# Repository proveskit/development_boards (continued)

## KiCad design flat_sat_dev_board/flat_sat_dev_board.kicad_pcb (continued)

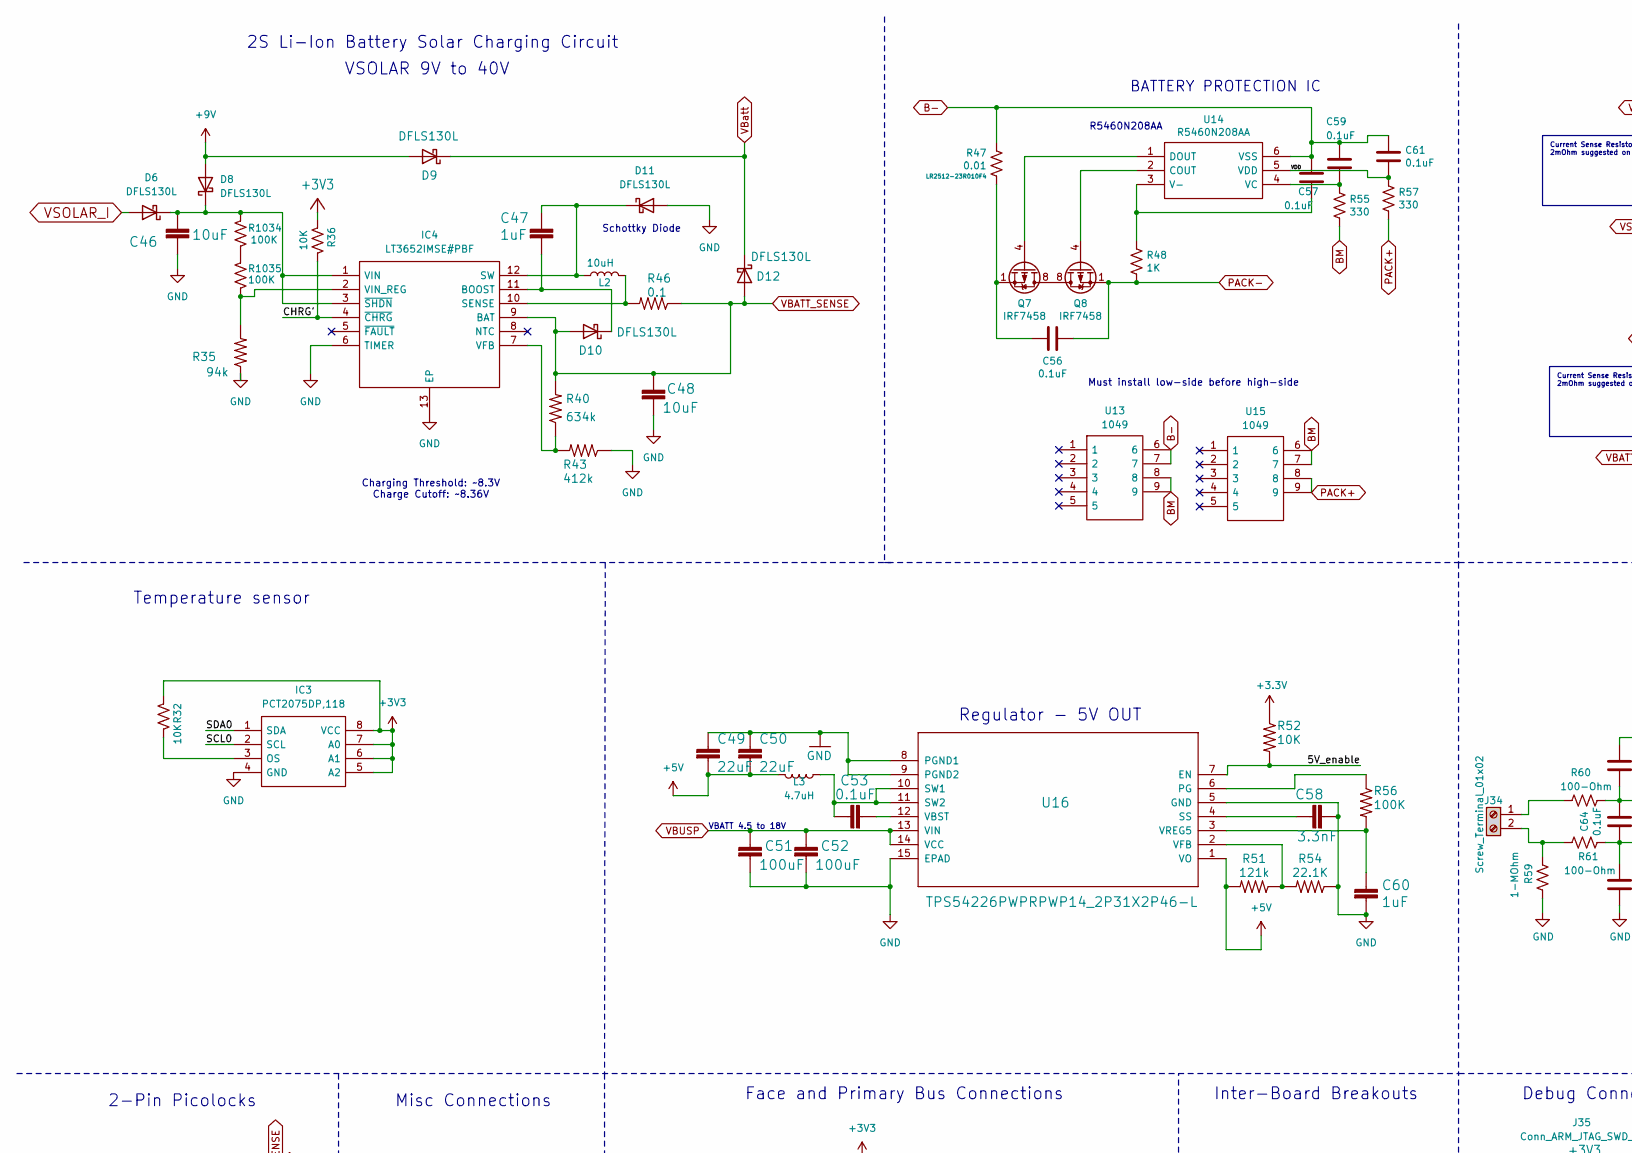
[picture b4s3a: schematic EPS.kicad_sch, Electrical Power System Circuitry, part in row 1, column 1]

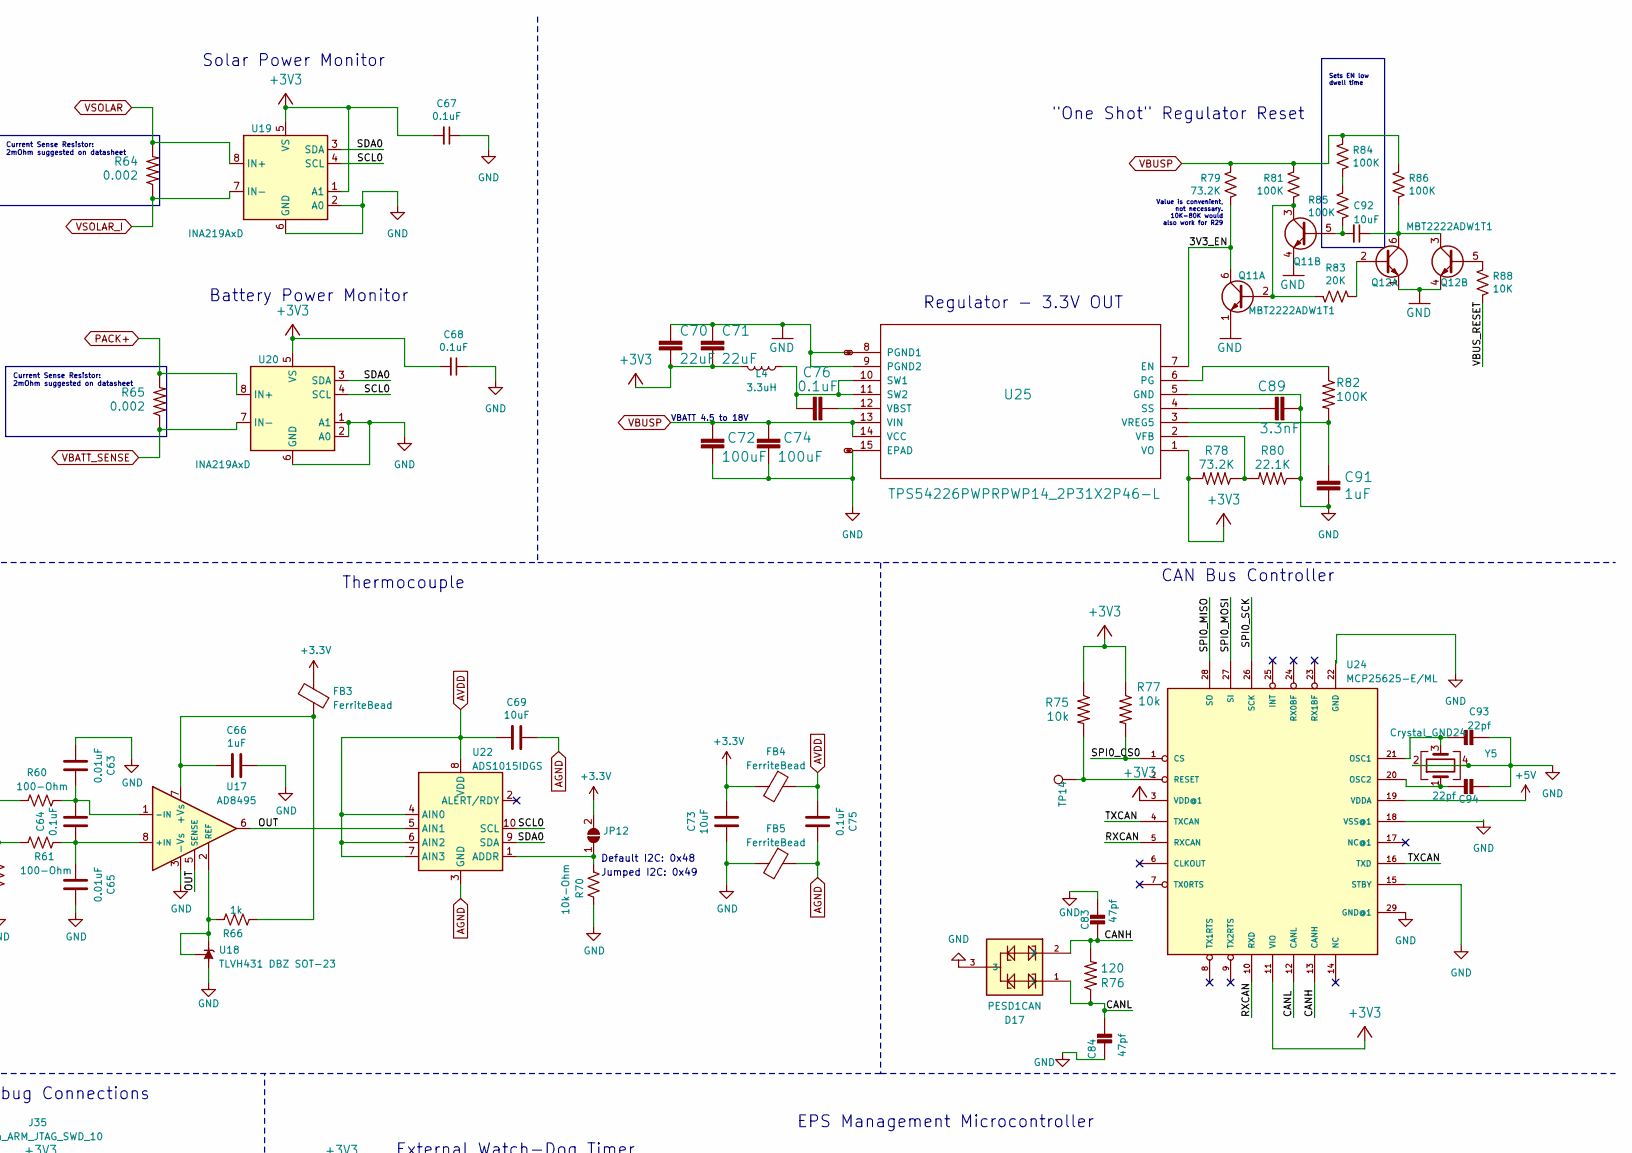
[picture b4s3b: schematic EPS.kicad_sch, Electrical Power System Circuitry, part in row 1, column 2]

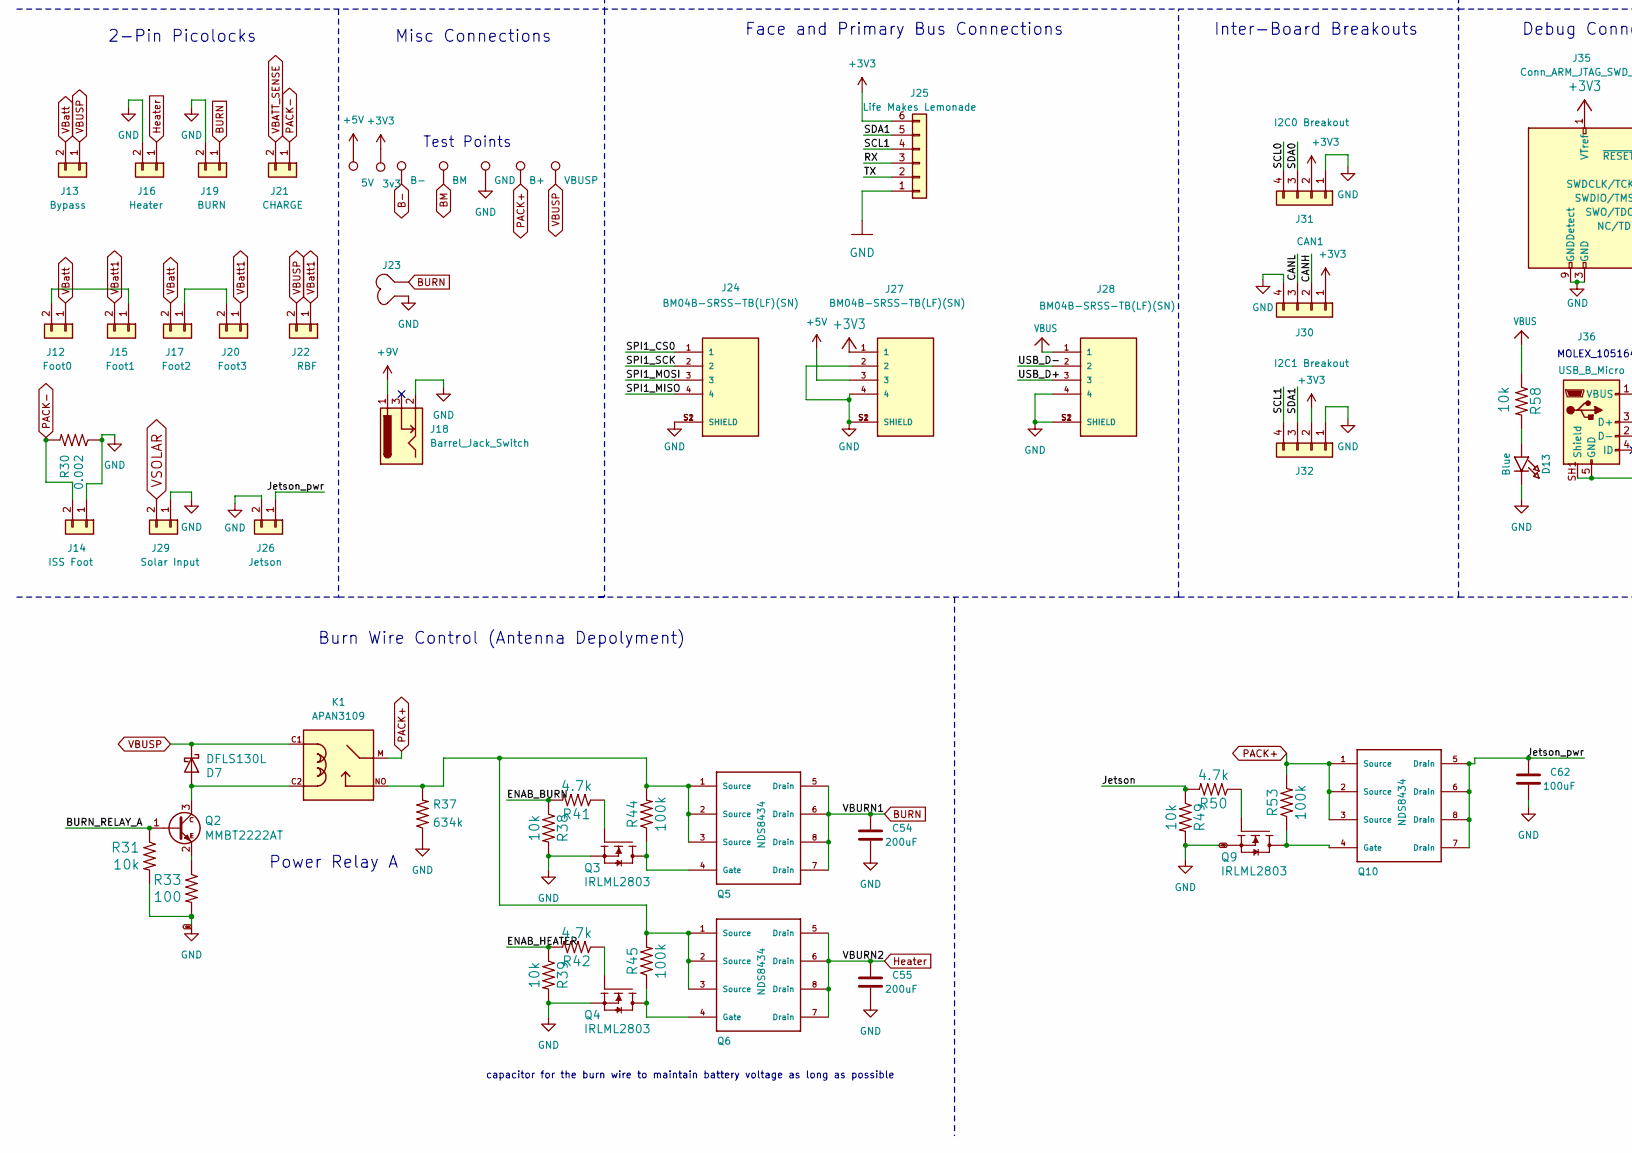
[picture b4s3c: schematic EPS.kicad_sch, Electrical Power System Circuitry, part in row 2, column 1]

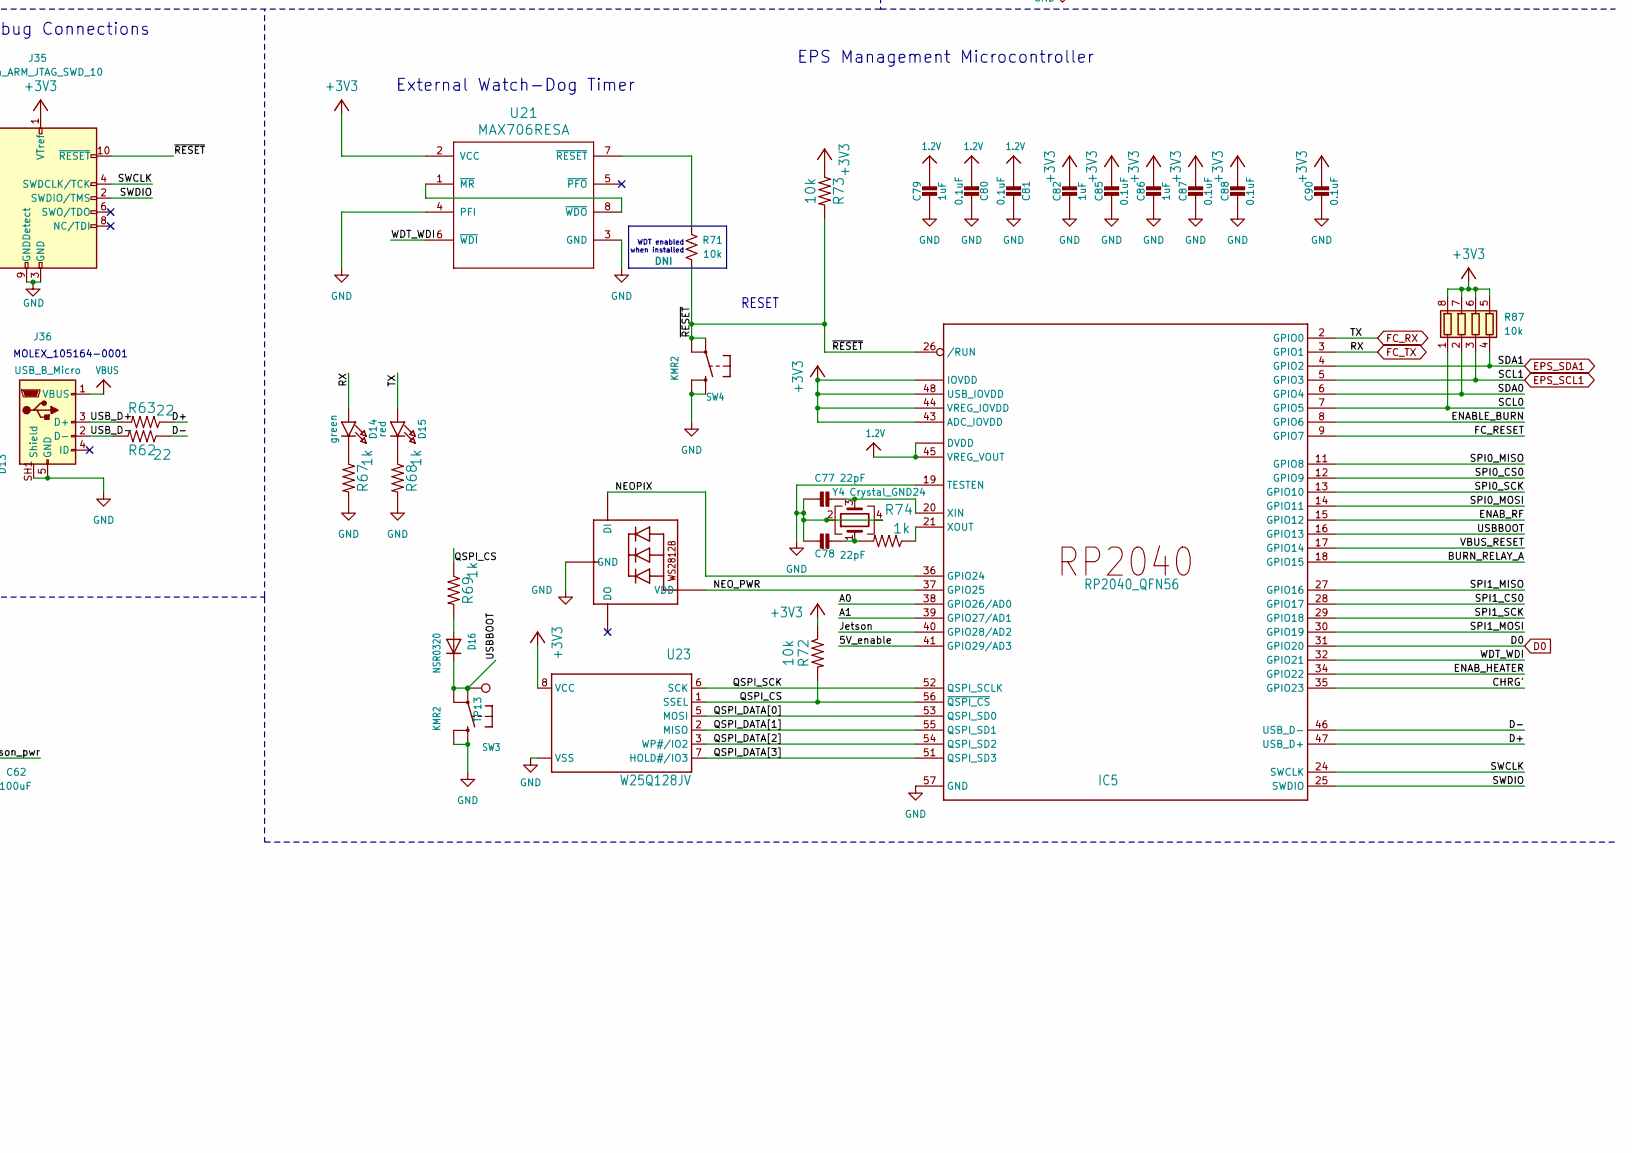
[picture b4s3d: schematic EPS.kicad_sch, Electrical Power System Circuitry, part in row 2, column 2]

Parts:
C46, C48, C92: 10uF; C_0603_1608Metric
C47, C60, C79, C82, C86, C91: 1uF; C_0603_1608Metric
C49, C50, C70, C71: 22uF; C_0603_1608Metric
C51, C52, C62, C72, C74: 100uF; C_1210_3225Metric
C53, C56, C57, C59, C61, C67, C68, C76: 0.1uF; C_0603_1608Metric
C54, C55: 200uF; C_1210_3225Metric
C58, C89: 3.3nF; C_0603_1608Metric
C63, C65: 0.01uF; C_0805_2012Metric
C64, C75: 0.1uF; C_0805_2012Metric
C66: 1uF; C_0805_2012Metric
C69, C73: 10uF; C_0805_2012Metric
C77, C78: 22pF; C_0402_1005Metric
C80, C81, C85, C87, C88, C90: 0.1uF; C_0402_1005Metric
C83, C84: 47pf; C_0402_1005Metric
C93, C94: 22pf; C_0402_1005Metric
D6, D8, D11: DFLS130L; D_PowerDI-123
D7, D9, D10, D12: DFLS130L; D_PowerDI-123; Manufacturer_Part_Number DFLS130L-7
D13: Blue; D_0603_1608Metric_Pad1.05x0.95mm_HandSolder
D14: green; D_0603_1608Metric_Pad1.05x0.95mm_HandSolder
D15: red; D_0603_1608Metric_Pad1.05x0.95mm_HandSolder
D16: NSR0320; D_SOD-323F
D17: PESD1CAN; SOT-23-3
FB3, FB4, FB5: FerriteBead; R_0603_1608Metric
IC3: PCT2075DP,118; TSSOP-8_3x3mm_P0.65mm; Mouser Part Number 771-PCT2075DP118
IC4: LT3652IMSE#PBF; MSOP-12-1EP_3x4mm_P0.65mm_EP1.65x2.85mm; Mouser Part Number 584-LT3652IMSE#PBF
IC5: RP2040_QFN56; QFN-56-1EP_7x7mm_P0.4mm_EP3.2x3.2mm
J12: Foot0; MOLEX_504050-0291
J13: Bypass; PinSocket_1x02_P2.54mm_Vertical
J14: ISS Foot; MOLEX_504050-0291
J15: Foot1; MOLEX_504050-0291
J16: Heater; MOLEX_504050-0291
J17: Foot2; MOLEX_504050-0291
J18: Barrel_Jack_Switch; BarrelJack_GCT_DCJ200-10-A_Horizontal
J19: BURN; MOLEX_504050-0291
J20: Foot3; MOLEX_504050-0291
J21: CHARGE; MOLEX_504050-0291
J22: RBF; MOLEX_504050-0291
J23: Burn_Wire
J24, J27, J28: BM04B-SRSS-TB(LF)(SN); JST_BM04B-SRSS-TB(LF)(SN); PARTREV N/A
J25: Life Makes Lemonade; PinHeader_1x06_P2.54mm_Vertical
J26: Jetson; MOLEX_504050-0291
J29: Solar Input; MOLEX_504050-0291
J30: CAN1; JST_SH_BM04B-SRSS-TB_1x04-1MP_P1.00mm_Vertical
J31: I2C0 Breakout; JST_SH_SM04B-SRSS-TB_1x04-1MP_P1.00mm_Horizontal
J32: I2C1 Breakout; JST_SH_BM04B-SRSS-TB_1x04-1MP_P1.00mm_Vertical
J34: Screw_Terminal_01x02; ScrewTerminal
J35: Conn_ARM_JTAG_SWD_10; JTAG_2X05_1.27MM_BOX_NOCREAM
J36: USB_B_Micro; MOLEX_105164-0001
JP12: SolderJumper_2_Open; SolderJumper-2_P1.3mm_Open_RoundedPad1.0x1.5mm
K1: APAN3109; RELAY_APAN3105
L2: 10uH; L_1812_4532Metric; Manufacturer_Part_Number SNR5040K-330M
L3: 4.7uH; L_1812_4532Metric; Manufacturer_Part_Number HPC5040NF-3R3MTH
L4: 3.3uH; L_1812_4532Metric; Manufacturer_Part_Number HPC5040NF-3R3MTH
LED2: WS2812B_SK6812_1515; LED_WS2812B_PLCC4_5.0x5.0mm_P3.2mm
Q2: MMBT2222AT; SOT-523; Manufacturer_Part_Number MMBT2222ALT1G
Q3, Q4, Q9: IRLML2803; SOT-23; Manufacturer_Part_Number MMBT2222AT
Q5, Q6, Q10: NDS8434; SOIC-8-1EP_3.9x4.9mm_P1.27mm_EP2.514x3.2mm; Manufacturer_Part_Number NDS8434
Q7, Q8: IRF7458; SOIC-8_3.9x4.9mm_P1.27mm
Q11, Q12: MBT2222ADW1T1; SOT-363_SC-70-6; Manufacturer_Part_Number MBT2222ADW1T1G
R30, R64, R65: 0.002; R_2512_6332Metric
R31, R38, R39, R49, R58, R71, R72, R73, R75, R77: 10k; R_0603_1608Metric
R32, R36, R52, R88: 10K; R_0603_1608Metric
R33: 100; R_0603_1608Metric
R35: 94k; R_0603_1608Metric
R37, R40: 634k; R_0603_1608Metric
R41, R42, R50: 4.7k; R_0603_1608Metric
R43: 412k; R_0603_1608Metric
R44, R45, R53: 100k; R_0603_1608Metric
R46: 0.1; R_2512_6332Metric
R47: 0.01; R_2512_6332Metric
R48: 1K; R_0603_1608Metric
R51: 121k; R_0603_1608Metric
R54, R80: 22.1K; R_0603_1608Metric
R55, R57: 330; R_0603_1608Metric
R56, R81, R82, R84, R85, R86, R1034, R1035: 100K; R_0603_1608Metric
R59: 1-MOhm; R_0603_1608Metric
R60, R61: 100-Ohm; R_0603_1608Metric
R62, R63: 22; R_0603_1608Metric
R66, R67, R68, R69, R74: 1k; R_0603_1608Metric
R70: 10k-Ohm; R_0603_1608Metric
R76: 120; R_0603_1608Metric
R78, R79: 73.2K; R_0603_1608Metric
R83: 20K; R_0603_1608Metric
R87: 10k; R_Array_Convex_4x0603
SW3, SW4: KMR2; BTN_KMR2_4.6X2.8
TP6: 5V; TestPoint_Loop_D1.80mm_Drill1.0mm_Beaded
TP7: 3v3; TestPoint_Loop_D1.80mm_Drill1.0mm_Beaded
TP8: B-; TestPoint_Loop_D1.80mm_Drill1.0mm_Beaded
TP9: BM; TestPoint_Loop_D1.80mm_Drill1.0mm_Beaded
TP10: GND; TestPoint_Loop_D1.80mm_Drill1.0mm_Beaded
TP11: B+; TestPoint_Loop_D1.80mm_Drill1.0mm_Beaded
TP12: VBUSP; TestPoint_Loop_D1.80mm_Drill1.0mm_Beaded
TP13: USBBOOT; TestPoint_Loop_D1.80mm_Drill1.0mm_Beaded
TP14: RESET; TestPoint_Loop_D1.80mm_Drill1.0mm_Beaded
U13, U15: 1049; Mouser Part Number 534-1049
U14: R5460N208AA; SOT-23-6; Manufacturer_Part_Number R5460N233AF-TR-FE; Mouser Part Number 848-R5460N233AFTRFE
U16, U25: TPS54226PWPRPWP14_2P31X2P46-L; HTSSOP-14-1EP_4.4x5mm_P0.65mm_EP3.4x5mm_Mask3x3.1mm_Thermal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; Manufacturer_Part_Number TPS54226PWPR
U17: AD8495; MSOP-8_3x3mm_P0.65mm
U18: TLVH431 DBZ SOT-23; SOT-23
U19, U20: INA219AxD; SOIC-8_3.9x4.9mm_P1.27mm
U21: MAX706RESA; SO-8_3.9x4.9mm_P1.27mm; Manufacturer_Part_Number MAX706RESA
U22: ADS1015IDGS; TSSOP-10_3x3mm_P0.5mm
U23: W25Q128JV; SOIC-8_5.275x5.275mm_P1.27mm
U24: MCP25625-E/ML; QFN-28-1EP_6x6mm_P0.65mm_EP4.25x4.25mm
Y4, Y5: Crystal_GND24; Crystal_SMD_2520-4Pin_2.5x2.0mm

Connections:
1.2V: C79.1, C80.2, C81.2, IC5.23 (DVDD), IC5.45 (VREG_VOUT), IC5.50 (DVDD); also elsewhere on the board
+3.3V: C73.2, FB3.2, FB4.2, JP12.2 (B), R52.1
+3V3: C67.2, C68.2, C70.2, C71.2, C82.1, C85.1, C86.1, C87.1, C88.1, C90.1, IC3.5 (A2), IC3.6 (A1), IC3.7 (A0), IC3.8 (VCC), IC5.1 (IOVDD), IC5.10 (IOVDD), IC5.22 (IOVDD), IC5.33 (IOVDD), IC5.42 (IOVDD), IC5.43 (ADC_IOVDD), IC5.44 (VREG_IOVDD), IC5.48 (USB_IOVDD), IC5.49 (IOVDD), J25.6, J27.1, J30.1, J31.2, J32.2, J35.1 (VTref), L4.2, R32.1, R36.1, R72.1, R73.1, R75.1, R77.1, R78.2, R87.5 (R4.2), R87.6 (R3.2), R87.7 (R2.2), R87.8 (R1.2), TP7.1, U19.1 (A1), U19.5 (VS), U20.5 (VS), U21.2 (VCC), U23.8 (VCC), U24.3 (VDD@1), U24.11 (VIO), U25.1 (VO); also elsewhere on the board
+5V: C49.2, C50.2, J27.3, L3.2, R51.2, TP6.1, U16.1 (VO), U24.19 (VDDA); also elsewhere on the board
+9V: D8.2 (A), D9.2 (A), J18.1
/Electrical Power System Stuff/3V3_EN: Q11.6 (C1), R79.2, U25.7 (EN)
/Electrical Power System Stuff/5V_enable: IC5.41 (GPIO29/AD3), R52.2, U16.7 (EN)
/Electrical Power System Stuff/A0: IC5.38 (GPIO26/AD0)
/Electrical Power System Stuff/A1: IC5.39 (GPIO27/AD1)
/Electrical Power System Stuff/BURN_RELAY_A: IC5.18 (GPIO15), Q2.1 (B), R31.1
/Electrical Power System Stuff/CANH: C83.2, D17.2, J30.2, R76.2, U24.13 (CANH)
/Electrical Power System Stuff/CANL: C84.1, D17.1, J30.3, R76.1, U24.12 (CANL)
/Electrical Power System Stuff/CHRG': IC4.4 (~CHRG), IC5.35 (GPIO23), R36.2
/Electrical Power System Stuff/D+: IC5.47 (USB_D+), R63.1
/Electrical Power System Stuff/D-: IC5.46 (USB_D-), R62.1
/Electrical Power System Stuff/ENABLE_BURN: IC5.8 (GPIO6)
/Electrical Power System Stuff/ENAB_BURN: R38.1, R41.2
/Electrical Power System Stuff/ENAB_HEATER: IC5.34 (GPIO22), R39.1, R42.2
/Electrical Power System Stuff/ENAB_RF: IC5.15 (GPIO12)
/Electrical Power System Stuff/FC_RESET: IC5.9 (GPIO7)
/Electrical Power System Stuff/Jetson: IC5.40 (GPIO28/AD2), R49.1, R50.2
/Electrical Power System Stuff/Jetson_pwr: C62.1, J26.1, Q10.5 (Drain), Q10.6 (Drain), Q10.7 (Drain), Q10.8 (Drain)
/Electrical Power System Stuff/NEOPIX: IC5.36 (GPIO24), LED2.4 (DI)
/Electrical Power System Stuff/NEO_PWR: IC5.37 (GPIO25), LED2.1 (VDD)
/Electrical Power System Stuff/OUT: U17.5 (SENSE), U17.6, U22.5 (AIN1)
/Electrical Power System Stuff/QSPI_CS: IC5.56 (~QSPI_CS), R69.1, R72.2, U23.1 (SSEL)
/Electrical Power System Stuff/QSPI_DATA[0]: IC5.53 (QSPI_SD0), U23.5 (MOSI)
/Electrical Power System Stuff/QSPI_DATA[1]: IC5.55 (QSPI_SD1), U23.2 (MISO)
/Electrical Power System Stuff/QSPI_DATA[2]: IC5.54 (QSPI_SD2), U23.3 (WP#/IO2)
/Electrical Power System Stuff/QSPI_DATA[3]: IC5.51 (QSPI_SD3), U23.7 (HOLD#/IO3)
/Electrical Power System Stuff/QSPI_SCK: IC5.52 (QSPI_SCLK), U23.6 (SCK)
/Electrical Power System Stuff/RXCAN: U24.5 (RXCAN), U24.10 (RXD)
/Electrical Power System Stuff/SCL0: IC3.2 (SCL), IC5.7 (GPIO5), J31.4, R87.1 (R1.1), U19.4 (SCL), U20.4 (SCL), U22.10 (SCL)
/Electrical Power System Stuff/SDA0: IC3.1 (SDA), IC5.6 (GPIO4), J31.3, R87.2 (R2.1), U19.3 (SDA), U20.3 (SDA), U22.9 (SDA)
/Electrical Power System Stuff/SPI0_CS0: IC5.12 (GPIO9), R77.2, U24.1 (CS)
/Electrical Power System Stuff/SPI0_MISO: IC5.11 (GPIO8), U24.28 (SO)
/Electrical Power System Stuff/SPI0_MOSI: IC5.14 (GPIO11), U24.27 (SI)
/Electrical Power System Stuff/SPI0_SCK: IC5.13 (GPIO10), U24.26 (SCK)
/Electrical Power System Stuff/SPI1_CS0: IC5.28 (GPIO17), J24.1
/Electrical Power System Stuff/SPI1_MISO: IC5.27 (GPIO16), J24.4
/Electrical Power System Stuff/SPI1_MOSI: IC5.30 (GPIO19), J24.3
/Electrical Power System Stuff/SPI1_SCK: IC5.29 (GPIO18), J24.2
/Electrical Power System Stuff/SWCLK: IC5.24 (SWCLK), J35.4 (SWDCLK/TCK)
/Electrical Power System Stuff/SWDIO: IC5.25 (SWDIO), J35.2 (SWDIO/TMS)
/Electrical Power System Stuff/TXCAN: U24.4 (TXCAN), U24.16 (TXD)
/Electrical Power System Stuff/USBBOOT: D16.1, IC5.16 (GPIO13), SW3.A, SW3.A' (P1), TP13.1
/Electrical Power System Stuff/USB_D+: J28.3, J36.3 (D+), R63.2
/Electrical Power System Stuff/USB_D-: J28.2, J36.2 (D-), R62.2
/Electrical Power System Stuff/VBUS_RESET: IC5.17 (GPIO14), R88.2
/Electrical Power System Stuff/VDD: C61.2, R57.2, U14.5 (VDD)
/Electrical Power System Stuff/WDT_WDI: IC5.32 (GPIO21), U21.6 (~WDI)
/Electrical Power System Stuff/~RESET: IC5.26 (/RUN), J35.10 (~RESET), R71.1, R73.2, SW4.A, SW4.A' (P1)
AGND: C69.2, C75.2, FB5.1, U22.3 (GND)
AVDD: C69.1, C75.1, FB4.1, U22.4 (AIN0), U22.6 (AIN2), U22.7 (AIN3), U22.8 (VDD)
B-: C57.1, C59.1, C61.1, R47.1, TP8.1, U13.6, U13.7, U14.6 (VSS)
BM: R55.1, TP9.1, U13.8, U13.9, U15.6, U15.7
BURN: C54.1, J19.1, J23.1 (Power), Q5.5 (Drain), Q5.6 (Drain), Q5.7 (Drain), Q5.8 (Drain)
D0: IC5.31 (GPIO20); also elsewhere on the board
EPS_SCL1: IC5.5 (GPIO3), J25.4, J32.4, R87.3 (R3.1); also elsewhere on the board
EPS_SDA1: IC5.4 (GPIO2), J25.5, J32.3, R87.4 (R4.1); also elsewhere on the board
FC_RX: D15.2, IC5.2 (GPIO0), J25.2; also elsewhere on the board
FC_TX: D14.2, IC5.3 (GPIO1), J25.3; also elsewhere on the board
GND: C46.2, C48.2, C49.1, C50.1, C51.2, C52.2, C54.2, C55.2, C58.2, C60.2, C62.2, C63.1, C65.2, C66.2, C67.1, C68.1, C70.1, C71.1, C72.2, C73.1, C74.2, C77.1, C78.1, C79.2, C80.1, C81.1, C82.2, C83.1, C84.2, C85.2, C86.2, C87.2, C88.2, C89.2, C90.2, C91.2, C93.2, C94.2, D11.2 (A), D13.1, D17.3, FB5.2, IC3.4 (GND), IC4.6 (TIMER), IC4.13 (EP), IC5.19 (TESTEN), IC5.57 (GND), J14.1, J16.2, J18.2, J19.2, J23.2 (GND), J24.S1 (SHIELD), J24.S2 (SHIELD), J25.1, J26.2, J27.2, J27.4, J27.S1 (SHIELD), J27.S2 (SHIELD), J28.4, J28.S1 (SHIELD), J28.S2 (SHIELD), J29.1, J30.4, J31.1, J32.1, J35.3 (GND), J35.5 (GND), J35.9 (GNDDetect), J36.5 (GND), J36.SH1 (Shield), LED2.3 (GND), Q3.2 (S), Q4.2 (S), Q9.2 (S), Q11.1 (E1), Q11.4 (E2), Q12.1 (E1), Q12.4 (E2), R30.1, R31.2, R33.2, R35.1, R37.1, R38.2, R39.2, R43.1, R49.2, R54.1, R59.2, R67.2, R68.2, R70.1, R80.1, SW3.B (S), SW3.B' (S1), SW4.B (S), SW4.B' (S1), TP10.1, U16.5 (GND), U16.8 (PGND1), U16.9 (PGND2), U16.15 (EPAD), U17.3 (-Vs), U18.3 (A), U19.2 (A0), U19.6 (GND), U20.1 (A1), U20.2 (A0), U20.6 (GND), U21.3 (GND), U21.4 (PFI), U23.4 (VSS), U23.PAD (VSS), U24.15 (STBY), U24.18 (VSS@1), U24.22 (GND), U24.29 (GND@1), U25.5 (GND), U25.8 (PGND1), U25.9 (PGND2), U25.15 (EPAD), Y4.2, Y4.4, Y5.2, Y5.4; also elsewhere on the board
Heater: C55.1, J16.1, Q6.5 (Drain), Q6.6 (Drain), Q6.7 (Drain), Q6.8 (Drain)
unnamed: C56.1, Q7.1 (S), Q7.2 (S), Q7.3 (S), R47.2
unnamed: C78.2, R74.2, Y4.1
unnamed: C46.1, D6.1 (K), D8.1 (K), IC4.1 (VIN), IC4.3 (~SHDN), R1034.1
unnamed: D7.2 (A), K1.C2, Q2.3 (C)
unnamed: C47.2, D10.1 (K), IC4.11 (BOOST)
unnamed: C47.1, D11.1 (K), IC4.12 (SW), L2.1
unnamed: D13.2, R58.2
unnamed: D14.1, R67.1
unnamed: D15.1, R68.1
unnamed: D16.2, R69.2
unnamed: IC3.3 (OS), R32.2
unnamed: IC4.10 (SENSE), L2.2, R46.2
unnamed: IC4.7 (VFB), R40.1, R43.2
unnamed: IC4.2 (VIN_REG), R35.2, R1035.2
unnamed: C77.2, IC5.20 (XIN), Y4.3
unnamed: IC5.21 (XOUT), R74.1
unnamed: J12.2, J15.1
unnamed: J17.1, J20.2
unnamed: J34.1, R60.1
unnamed: J34.2, R59.1, R61.2
unnamed: JP12.1 (A), R70.2, U22.1 (ADDR)
unnamed: K1.NO, Q5.1 (Source), Q5.2 (Source), Q5.3 (Source), Q6.1 (Source), Q6.2 (Source), Q6.3 (Source), R37.2, R44.2, R45.2
unnamed: Q2.2 (E), R33.1
unnamed: Q3.3 (D), Q5.4 (Gate), R44.1
unnamed: Q3.1 (G), R41.1
unnamed: Q4.3 (D), Q6.4 (Gate), R45.1
unnamed: Q4.1 (G), R42.1
unnamed: Q7.5 (D), Q7.6 (D), Q7.7 (D), Q7.8 (D), Q8.5 (D), Q8.6 (D), Q8.7 (D), Q8.8 (D)
unnamed: Q7.4 (G), U14.1 (DOUT)
unnamed: Q8.4 (G), U14.2 (COUT)
unnamed: Q9.1 (G), R50.1
unnamed: Q9.3 (D), Q10.4 (Gate), R53.1
unnamed: Q11.2 (B1), Q11.3 (C2), R81.2, R83.2
unnamed: C92.2, Q11.5 (B2), R85.2
unnamed: Q12.2 (B1), R83.1
unnamed: C92.1, Q12.3 (C2), Q12.6 (C1), R86.2
unnamed: Q12.5 (B2), R88.1
unnamed: R84.2, R85.1
unnamed: R1034.2, R1035.1
unnamed: C57.2, R48.1, U14.3 (V-)
unnamed: C59.2, R55.2, U14.4 (VC)
unnamed: R56.1, U16.6 (PG)
unnamed: C58.1, U16.4 (SS)
unnamed: C53.1, L3.1, U16.10 (SW1), U16.11 (SW2)
unnamed: C53.2, U16.12 (VBST)
unnamed: R51.1, R54.2, U16.2 (VFB)
unnamed: C60.1, R56.2, U16.3 (VREG5)
unnamed: C64.1, C65.1, R61.1, U17.8 (+IN)
unnamed: C66.1, FB3.1, R66.2, U17.7 (+Vs)
unnamed: C63.2, C64.2, R60.2, U17.1 (-IN)
unnamed: R66.1, U17.2 (REF), U18.1 (K), U18.2 (REF)
unnamed: U21.1 (~MR), U21.8 (~WDO)
unnamed: R71.2, U21.7 (~RESET)
unnamed: C93.1, U24.21 (OSC1), Y5.3
unnamed: C94.1, U24.20 (OSC2), Y5.1
unnamed: R75.2, TP14.1, U24.2 (RESET)
unnamed: R82.1, U25.6 (PG)
unnamed: C89.1, U25.4 (SS)
unnamed: C76.1, L4.1, U25.10 (SW1), U25.11 (SW2)
unnamed: C76.2, U25.12 (VBST)
unnamed: R78.1, R80.2, U25.2 (VFB)
unnamed: C91.1, R82.2, U25.3 (VREG5)
PACK+: K1.M, Q10.1 (Source), Q10.2 (Source), Q10.3 (Source), R53.2, R57.1, R65.2, TP11.1, U15.8, U15.9, U20.8 (IN+)
PACK-: C56.2, J14.2, J21.1, Q8.1 (S), Q8.2 (S), Q8.3 (S), R30.2, R48.2
VBATT_SENSE: C48.1, D10.2 (A), D12.2 (A), IC4.9 (BAT), J21.2, R40.2, R46.1, R65.1, U20.7 (IN-)
VBUS: J28.1, J36.1 (VBUS), R58.1
VBUSP: C51.1, C52.1, C72.1, C74.1, D7.1 (K), J13.1, J22.2, K1.C1, R79.1, R81.1, R84.1, R86.1, TP12.1, U16.13 (VIN), U16.14 (VCC), U25.13 (VIN), U25.14 (VCC)
VBatt: D9.1 (K), D12.1 (K), J12.1, J13.2, J17.2
VBatt1: J15.2, J20.1, J22.1
VSOLAR: J29.2, R64.2, U19.8 (IN+)
VSOLAR_I: D6.2 (A), R64.1, U19.7 (IN-)

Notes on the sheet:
Must install low-side before high-side
Test Points
EPS Management Microcontroller
RESET
Current Sense Resistor: 2mOhm suggested on datasheet
"One Shot" Regulator Reset
VSOLAR 9V to 40V
Regulator - 3.3V OUT
Battery Power Monitor
CAN Bus Controller
Solar Power Monitor
WDT enabled when installed
Sets EN low dwell time
Jumped I2C: 0x49
BATTERY PROTECTION IC
Default I2C: 0x48
Misc Connections
2S Li-Ion Battery Solar Charging Circuit
Face and Primary Bus Connections
Thermocouple
2-Pin Picolocks
MOLEX_105164-0001
R5460N208AA
External Watch-Dog Timer
Burn Wire Control (Antenna Depolyment)
Temperature sensor
Debug Connections
Power Relay A
capacitor for the burn wire to maintain battery voltage as long as possible
Value is convenient, not necessary. 10K-80K would also work for R29
Schottky Diode
VBATT 4.5 to 18V
Charging Threshold: ~8.3V Charge Cutoff: ~8.36V
Regulator - 5V OUT
Inter-Board Breakouts

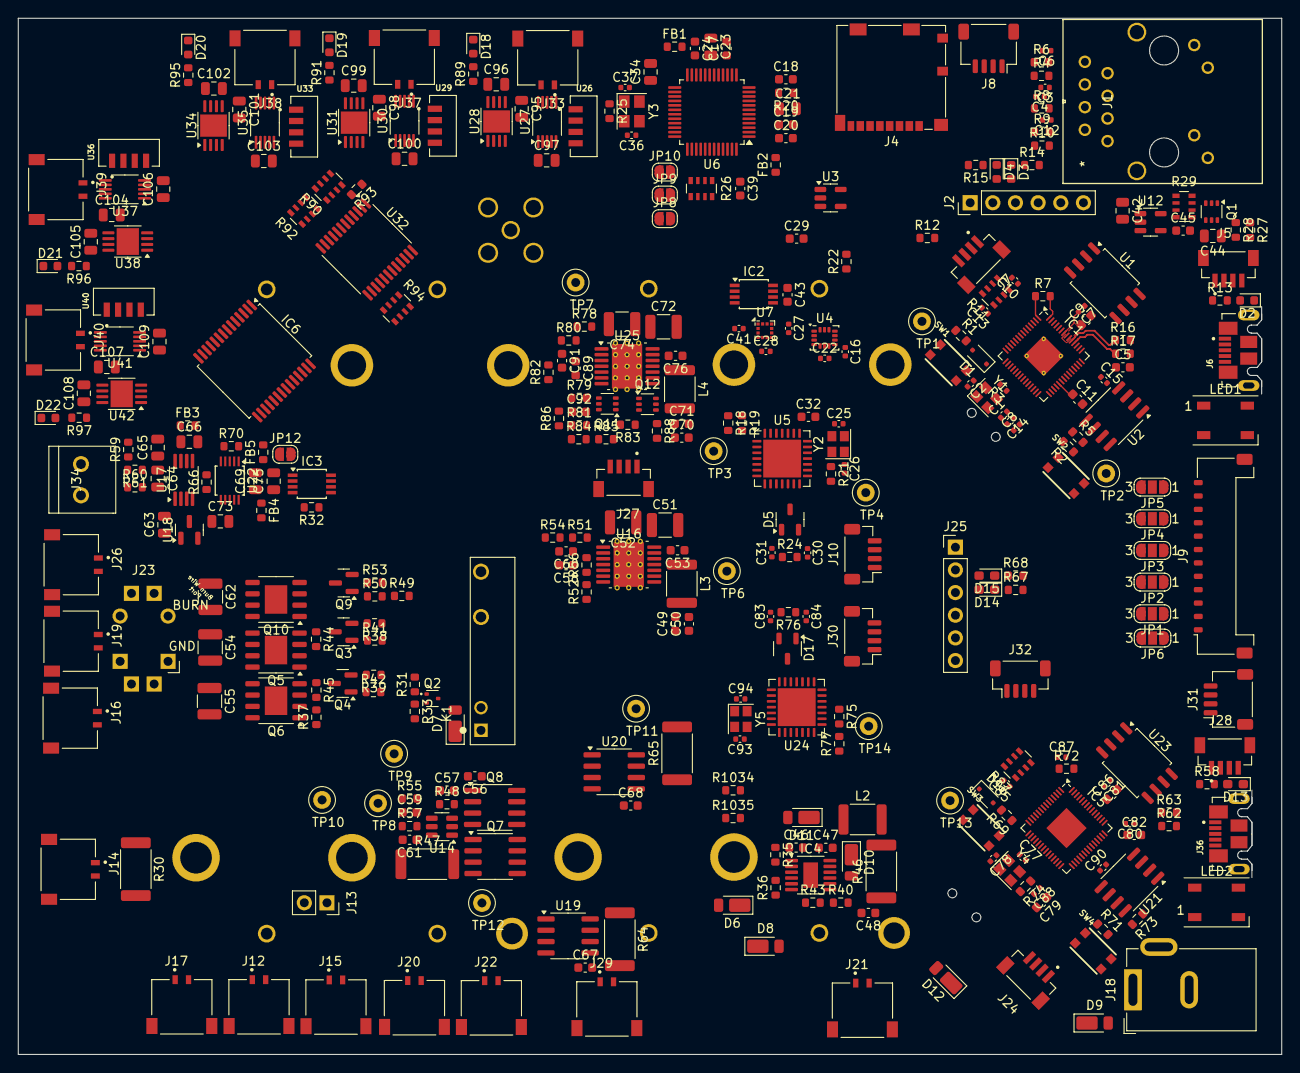
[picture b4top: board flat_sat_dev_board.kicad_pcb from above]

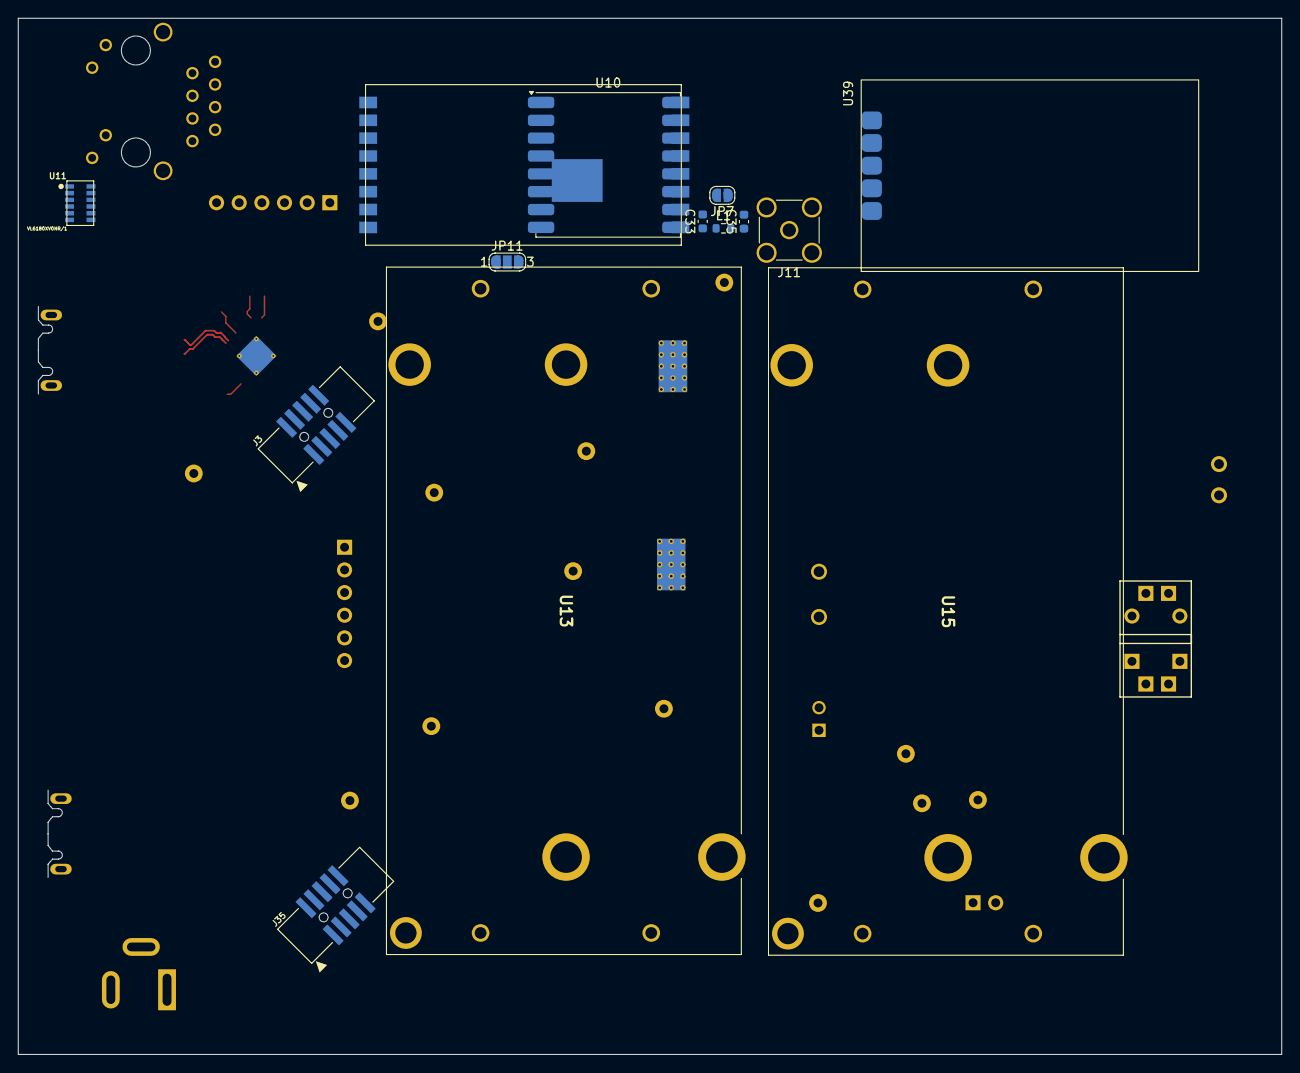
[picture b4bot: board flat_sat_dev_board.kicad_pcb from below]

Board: 4 copper layers, 141.6 x 116.1 mm, 371 parts (14 on the bottom side), 264 nets.

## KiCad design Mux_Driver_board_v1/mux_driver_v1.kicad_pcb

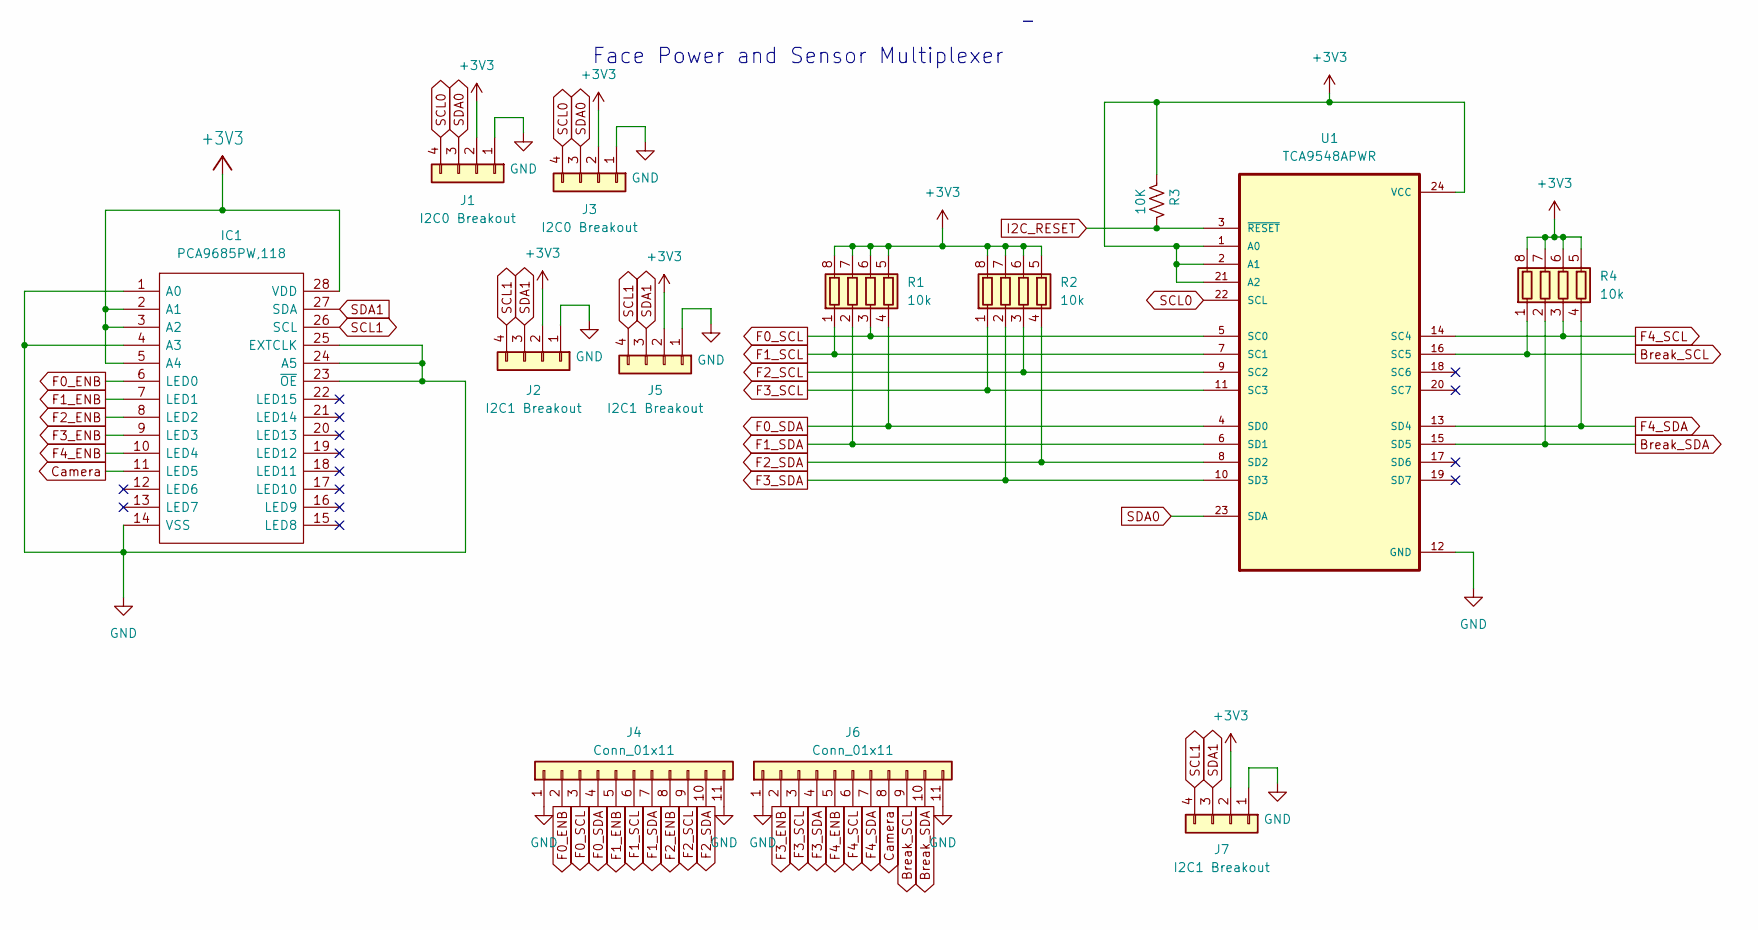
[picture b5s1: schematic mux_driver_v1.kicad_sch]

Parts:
IC1: PCA9685PW,118; SOP65P640X110-28N; Mouser Part Number 771-PCA9685PW,118
J1, J3: I2C0 Breakout; JST_SH_BM04B-SRSS-TB_1x04-1MP_P1.00mm_Vertical
J2, J5: I2C1 Breakout; JST_SH_BM04B-SRSS-TB_1x04-1MP_P1.00mm_Vertical
J4, J6: Conn_01x11; PinHeader_1x11_P2.54mm_Vertical
J7: I2C1 Breakout; PinHeader_1x04_P2.54mm_Vertical
R1, R2, R4: 10k; R_Array_Convex_4x0603
R3: 10K; R_0603_1608Metric
U1: TCA9548APWR; SOP65P640X120-24N

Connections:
+3V3: IC1.2 (A1), IC1.3 (A2), IC1.5 (A4), IC1.28 (VDD), J1.2, J2.2, J3.2, J5.2, J7.2, R1.5 (R4.2), R1.6 (R3.2), R1.7 (R2.2), R1.8 (R1.2), R2.5 (R4.2), R2.6 (R3.2), R2.7 (R2.2), R2.8 (R1.2), R3.1, R4.5 (R4.2), R4.6 (R3.2), R4.7 (R2.2), R4.8 (R1.2), U1.1 (A0), U1.2 (A1), U1.21 (A2), U1.24 (VCC)
Break_SCL: J6.9, R4.1 (R1.1), U1.16 (SC5)
Break_SDA: J6.10, R4.2 (R2.1), U1.15 (SD5)
Camera: IC1.11 (LED5), J6.8
F0_ENB: IC1.6 (LED0), J4.2
F0_SCL: J4.3, R1.3 (R3.1), U1.5 (SC0)
F0_SDA: J4.4, R1.4 (R4.1), U1.4 (SD0)
F1_ENB: IC1.7 (LED1), J4.5
F1_SCL: J4.6, R1.1 (R1.1), U1.7 (SC1)
F1_SDA: J4.7, R1.2 (R2.1), U1.6 (SD1)
F2_ENB: IC1.8 (LED2), J4.8
F2_SCL: J4.9, R2.3 (R3.1), U1.9 (SC2)
F2_SDA: J4.10, R2.4 (R4.1), U1.8 (SD2)
F3_ENB: IC1.9 (LED3), J6.2
F3_SCL: J6.3, R2.1 (R1.1), U1.11 (SC3)
F3_SDA: J6.4, R2.2 (R2.1), U1.10 (SD3)
F4_ENB: IC1.10 (LED4), J6.5
F4_SCL: J6.6, R4.3 (R3.1), U1.14 (SC4)
F4_SDA: J6.7, R4.4 (R4.1), U1.13 (SD4)
GND: IC1.1 (A0), IC1.4 (A3), IC1.14 (VSS), IC1.23 (~OE), IC1.24 (A5), IC1.25 (EXTCLK), J1.1, J2.1, J3.1, J4.1, J4.11, J5.1, J6.1, J6.11, J7.1, U1.12 (GND)
I2C_RESET: R3.2, U1.3 (~RESET)
SCL0: J1.4, J3.4, U1.22 (SCL)
SCL1: IC1.26 (SCL), J2.4, J5.4, J7.4
SDA0: J1.3, J3.3, U1.23 (SDA)
SDA1: IC1.27 (SDA), J2.3, J5.3, J7.3

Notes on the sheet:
Face Power and Sensor Multiplexer

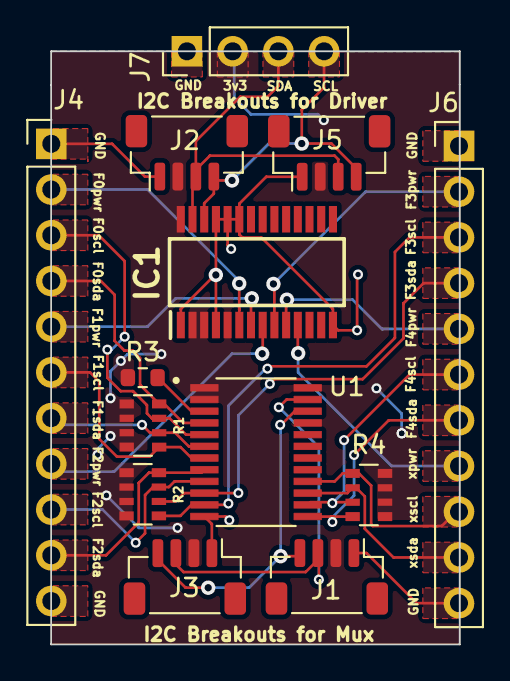
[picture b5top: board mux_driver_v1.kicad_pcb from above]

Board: 2 copper layers, 22.7 x 33.0 mm, 13 parts (0 on the bottom side), 25 nets.

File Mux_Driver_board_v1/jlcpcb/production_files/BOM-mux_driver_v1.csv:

Comment,Designator,Footprint,LCSC
TCA9548APWR,U1,SOP65P640X120-24N,C130026
I2C0 Breakout,"J1,J2,J3,J5",JST_SH_BM04B-SRSS-TB_1x04-1MP_P1.00mm_Vertical,C160390
10K,R3,R_0603_1608Metric,C25804
"PCA9685PW,118",IC1,SOP65P640X110-28N,C2678753
10k,"R1,R2,R4",R_Array_Convex_4x0603,C29718
Conn_01x11,J6,PinHeader_1x11_P2.54mm_Vertical,
Conn_01x11,J4,PinHeader_1x11_P2.54mm_Vertical,
I2C1 Breakout,J7,PinHeader_1x04_P2.54mm_Vertical,
